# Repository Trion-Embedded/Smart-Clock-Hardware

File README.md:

# Smart-Clock-Hardware
ESP32 based clock which includes clock, alarm, timer and task manager.

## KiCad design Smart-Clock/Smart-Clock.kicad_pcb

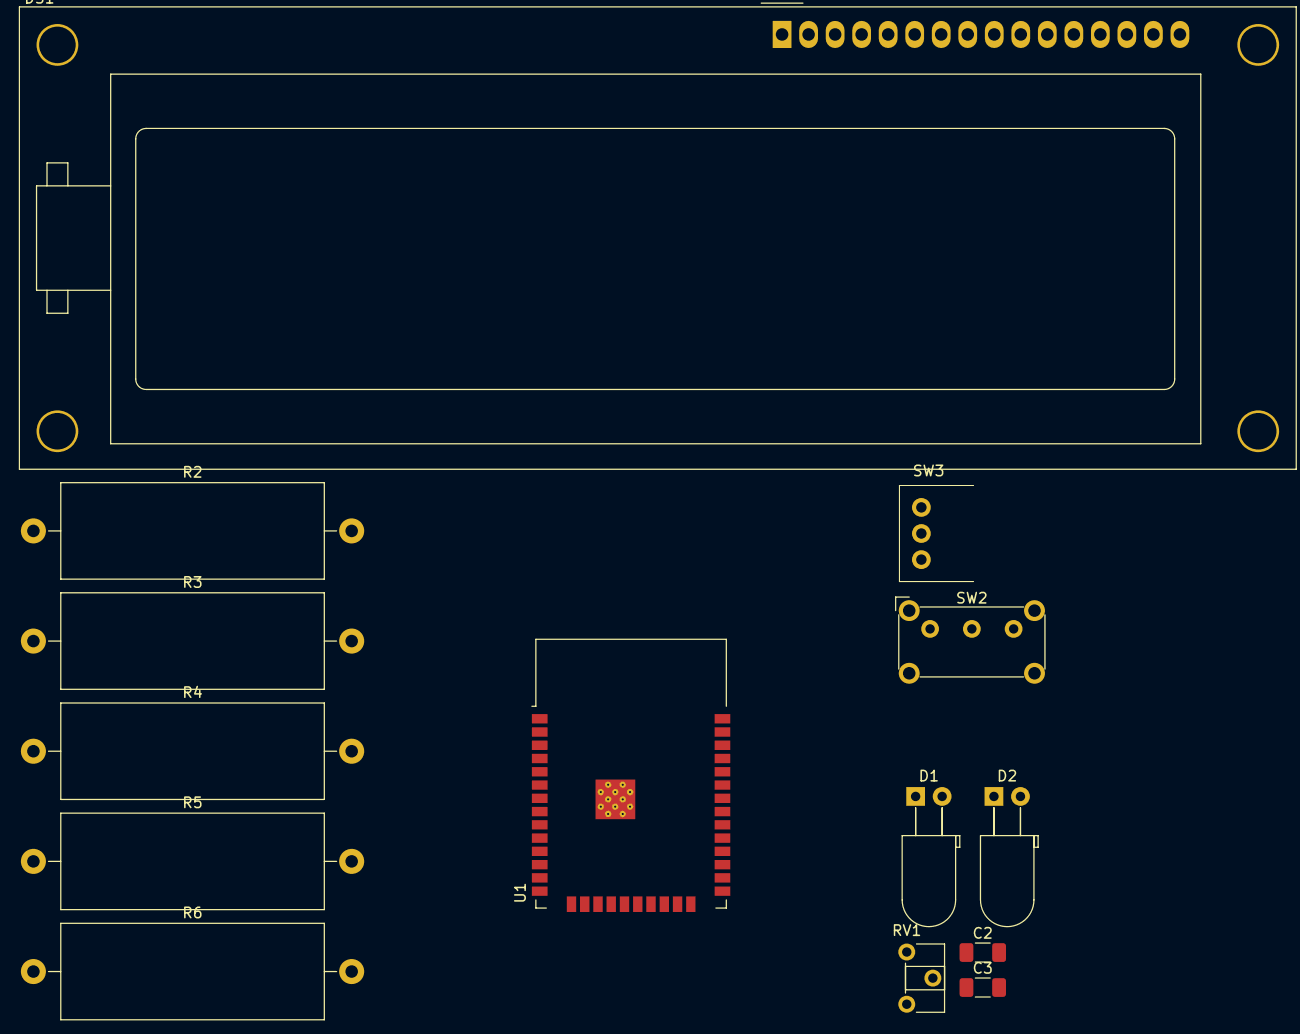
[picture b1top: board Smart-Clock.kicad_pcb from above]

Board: 2 copper layers, 14 parts (0 on the bottom side), 20 nets, no tracks yet.

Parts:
C2, C3: 10nF; C_1206_3216Metric_Pad1.33x1.80mm_HandSolder
D1: Yellow; LED_D5.0mm_Horizontal_O3.81mm_Z15.0mm
D2: Blue; LED_D5.0mm_Horizontal_O3.81mm_Z15.0mm
DS1: HY1602E
R2: 2k2; R_Axial_Power_L25.0mm_W9.0mm_P30.48mm
R3: 10k; R_Axial_Power_L25.0mm_W9.0mm_P30.48mm
R4, R5, R6: 330R; R_Axial_Power_L25.0mm_W9.0mm_P30.48mm
RV1: R_Potentiometer; Potentiometer_ACP_CA6-H2,5_Horizontal
SW2: SW_SPDT; SW_E-Switch_EG1224_SPDT_Angled
SW3: RotaryEncoder; RotaryEncoder_Bourns_Horizontal_PEC09-2xxxF-Nxxxx
U1: ESP32-WROOM-32D

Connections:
/A: C2.2, R3.1, U1.7 (IO35)
/B: C3.2, R4.1, U1.6 (IO34)
/C: SW3.C, U1.8 (IO32)
/D4: DS1.13 (DB4), U1.23 (IO15)
/D5: DS1.14 (DB5), U1.24 (IO2)
/D6: DS1.15 (DB6), U1.25 (IO0)
/D7: DS1.16 (DB7), U1.26 (IO4)
/EN: DS1.8 (E), U1.27 (IO16)
/LCD_PWR: DS1.4 (VDD), R2.1, RV1.3, SW2.2 (B)
/LED_B: D2.2 (A), U1.16 (IO13)
/LED_Y: D1.2 (A), U1.30 (IO18)
/REG_SEL: DS1.6 (RS), U1.14 (IO12)
GND: C2.1, C3.1, DS1.1 (LEDK), DS1.3 (VSS), DS1.7 (R/~W), R5.2, R6.2, RV1.1, SW2.3 (C), U1.1 (GND), U1.15 (GND), U1.38 (GND), U1.39 (GND)
unnamed: D1.1 (K), R6.1
unnamed: D2.1 (K), R5.1
unnamed: DS1.2 (LEDA), R2.2
unnamed: DS1.5 (Vo), RV1.2
unnamed: R3.2, SW3.A
unnamed: R4.2, SW3.B
VCC: SW2.1 (A), U1.2 (VDD)

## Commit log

2023-07-11 Fixed rotary encoder circuit.
2023-07-11 Updated drawing sheets and title blocks.
2023-07-11 Updated LCD Display.
2023-07-11 Deleted unused leds.
2023-07-11 ESP32 connections updated, usb-uart added and power circuit added.
2023-07-11 Added RGB status led.
2023-07-11 Update.
